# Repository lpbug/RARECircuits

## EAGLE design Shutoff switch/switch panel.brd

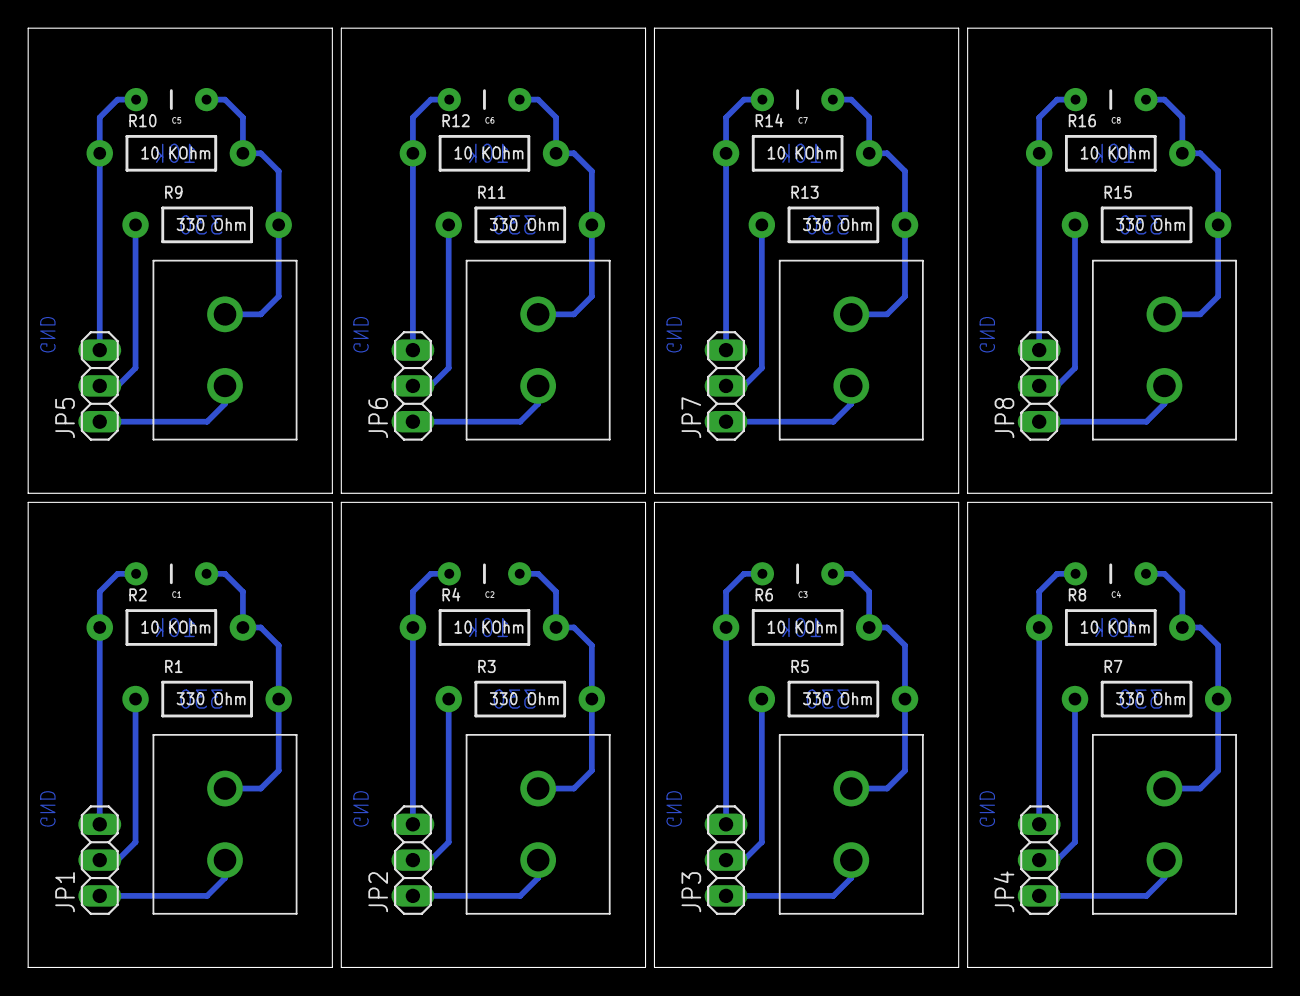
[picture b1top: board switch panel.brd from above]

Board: 2 copper layers, 88.3 x 66.7 mm, 40 parts (0 on the bottom side), 32 nets.

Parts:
C1, C2, C3, C4, C5, C6, C7, C8: 1uF; CAP-PTH-5MM
JP1, JP2, JP3, JP4, JP5, JP6, JP7, JP8: 1X03
R1, R3, R5, R7, R9, R11, R13, R15: 330 Ohm; AXIAL-0.4
R2, R4, R6, R8, R10, R12, R14, R16: 10 KOhm; AXIAL-0.4
U$1, U$2, U$3, U$4, U$5, U$6, U$7, U$8: CSAIL_PUSHBUTTON

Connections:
GND: C1.2, JP1.3, R2.P$1
GND1: C2.2, JP2.3, R4.P$1
GND2: C3.2, JP3.3, R6.P$1
GND3: C4.2, JP4.3, R8.P$1
GND4: C5.2, JP5.3, R10.P$1
GND5: C6.2, JP6.3, R12.P$1
GND6: C7.2, JP7.3, R14.P$1
GND7: C8.2, JP8.3, R16.P$1
unnamed: JP1.2, R1.P$1
unnamed: C1.1, R1.P$2, R2.P$2, U$1.P$2
unnamed: JP2.2, R3.P$1
unnamed: C2.1, R3.P$2, R4.P$2, U$2.P$2
unnamed: JP3.2, R5.P$1
unnamed: C3.1, R5.P$2, R6.P$2, U$3.P$2
unnamed: JP4.2, R7.P$1
unnamed: C4.1, R7.P$2, R8.P$2, U$4.P$2
unnamed: JP5.2, R9.P$1
unnamed: C5.1, R9.P$2, R10.P$2, U$5.P$2
unnamed: JP6.2, R11.P$1
unnamed: C6.1, R11.P$2, R12.P$2, U$6.P$2
unnamed: JP7.2, R13.P$1
unnamed: C7.1, R13.P$2, R14.P$2, U$7.P$2
unnamed: JP8.2, R15.P$1
unnamed: C8.1, R15.P$2, R16.P$2, U$8.P$2
VCC: JP1.1, U$1.P$1
VCC1: JP2.1, U$2.P$1
VCC2: JP3.1, U$3.P$1
VCC3: JP4.1, U$4.P$1
VCC4: JP5.1, U$5.P$1
VCC5: JP6.1, U$6.P$1
VCC6: JP7.1, U$7.P$1
VCC7: JP8.1, U$8.P$1

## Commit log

2015-05-15 Modified circuit for new switch added name and labeling

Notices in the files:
parts and their libraries:
SparkFun-Capacitors: Licensing: Creative Commons ShareAlike 4.0 International - https://creativecommons.org/licenses/by-sa/4.0
